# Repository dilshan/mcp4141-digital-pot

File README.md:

# MCP4141 based digital potentiometer

> MCP4141 and ATtiny13 based digital potentiometer to replace an
> existing 3 terminal analog potentiometers.

The main objective of this project is to create a prototype version of a digital potentiometer using *Microchip*'s MCP4141 IC. MCP4141 is available with end-to-end resistances of 5KΩ, 10KΩ, 50kΩ, and 100KΩ. This potentiometer-module can drive MCP4141 with any of the above mention resistances.

To drive the MCP4141, this module use ATtiny13 MCU. This MCU control MCP4141's resistance, based on the rotary-encoder events. ATtiny13 is an 8-pin, low power 8-bit MCU with an internal oscillator. The key reason to pick this MCU is its availability and lower price. Due to a lack of hardware-based SPI, this system use bit-banging SPI implementation to drive the MCP4141 IC. 

To reduce the board size, this module employs only 3 components. Which including ATtiny13, MCP4141, and rotary-encoder. The dimension of the PCB design given for this module is 26.16mm x 29.72mm. 

## Building and flash firmware

Firmware of this module is developed using AVR-GCC toolchain. To build the firmware execute the `make` command.

To flash the compiled firmware, use the following set of commands:

    make fuse
    make flash

The `make fuse` command can use to set up the fuse-bits of the MCU and it needs to execute only once.

## License

This is an open-source hardware project. Compiled firmware, PCB designs, schematic, and source codes related to this project are available at this repository. 

The firmware of this project is licensed under the terms of [MIT license](https://github.com/dilshan/mcp4141-digital-pot/blob/master/LICENSE). Hardware design and related content are licensed under [Creative Commons - Attribution 4.0 International](https://creativecommons.org/licenses/by/4.0/) ([CC BY 4.0](https://creativecommons.org/licenses/by/4.0/)) license.

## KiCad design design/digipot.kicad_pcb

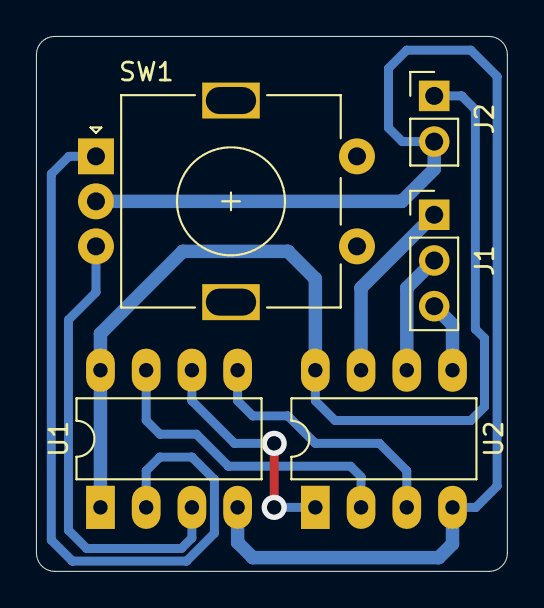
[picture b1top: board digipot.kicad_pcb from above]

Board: 2 copper layers, 26.2 x 29.7 mm, 5 parts (0 on the bottom side), 10 nets.

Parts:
J1: POT; PinHeader_1x03_P2.54mm_Vertical
J2: POWER; PinHeader_1x02_P2.54mm_Vertical
SW1: COM-09117; RotaryEncoder_Alps_EC11E-Switch_Vertical_H20mm
U1: ATtiny13; DIP-8_W7.62mm_LongPads
U2: MCP4141; DIP-8_W7.62mm_LongPads

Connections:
+5V: J2.1, U1.1, U1.8, U2.8
/CS: U1.6, U2.1
/MOSI: U1.5, U2.3
/SCK: U1.7, U2.2
GND: J2.2, SW1.C, U1.4, U2.4
unnamed: J1.1, U2.7
unnamed: J1.2, U2.6
unnamed: J1.3, U2.5
unnamed: SW1.A, U1.2
unnamed: SW1.B, U1.3

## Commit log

2020-03-27 Add firmware license file.
2020-03-27 Initial version of project readme file.
2020-03-27 Initial version of firmware and design files.
2020-03-27 Add schematic and breadboard views. :art:
